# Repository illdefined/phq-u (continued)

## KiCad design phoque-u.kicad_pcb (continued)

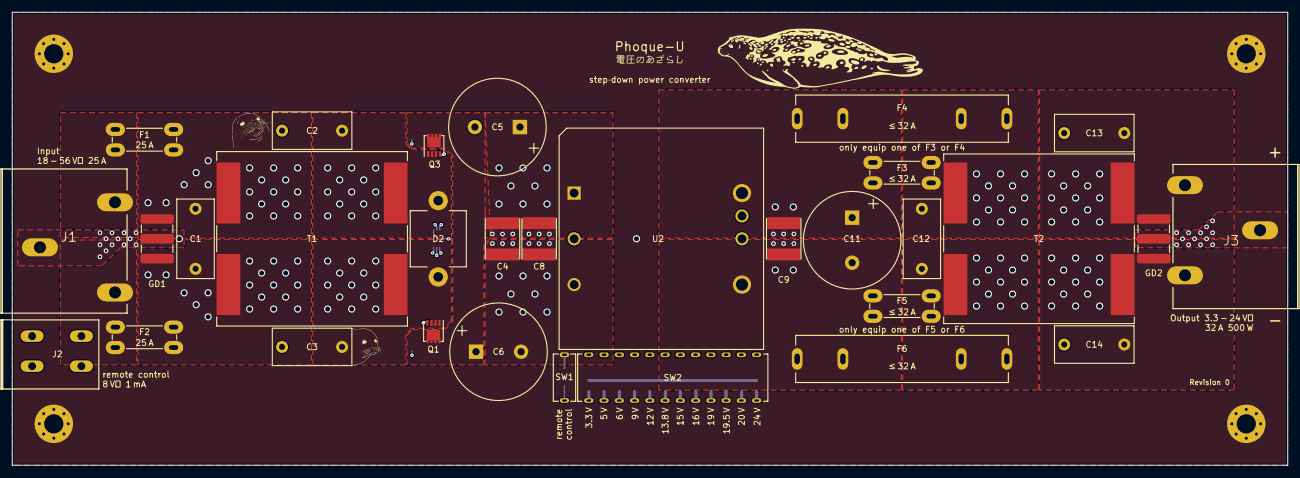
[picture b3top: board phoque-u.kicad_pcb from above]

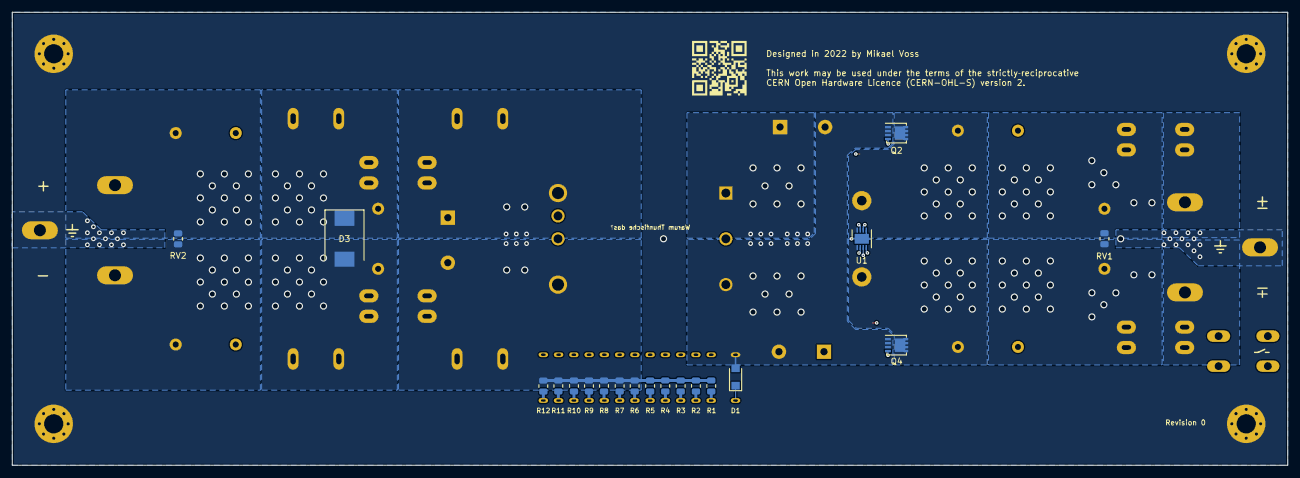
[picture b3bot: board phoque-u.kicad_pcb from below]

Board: 4 copper layers, 212.3 x 75.4 mm, 54 parts (19 on the bottom side), 33 nets.

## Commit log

2022-01-04 Initial import
2022-01-05 Update schematic according to parts availability
2022-01-05 Specify full part number for DC/DC module
2022-01-05 Add footprints
2022-01-05 Replace switches
2022-01-05 i7A4W033A033V: Remove pins 9 & 10
2022-01-05 Sir120DP: Remove pins 6, 7 & 8
2022-01-05 2606-1103: Correct pin numbers
2022-01-05 Remove film capacitors
2022-01-06 Remove test points
2022-01-07 Add initial PCB layout
2022-01-07 Optimise paths between rectifier and converter
2022-01-08 Add dedicated signal and ground layers
    This reduces the board dimensions considerably.
2022-01-08 Cut board to 212.3 × 75 cm
2022-01-08 Add missing 3D models
2022-01-08 Correct zone clearances
2022-01-08 Centre PCB
2022-01-08 Widen board for better fit and add mounting holes
2022-01-08 Customise PCB stackup
2022-01-09 Clean up silkscreen
2022-01-09 Reduce zone clearance to 0.2 mm
    Coating will be much more useful.
2022-01-09 Clear pads from silkscreen
2022-01-09 Attempt to optimise high‐current paths
2022-01-10 Finalise silkscreen
2022-01-10 Remove hyphen‐minus from project name
2022-01-10 Correct zone overlap
2022-01-10 Add JLC order number to silkscreen
2022-01-12 Add remote control circuit details to silkscreen
2022-01-24 Add external symbol and footprint library
2022-01-24 Revise schematic
    - Remove remote on/off connector,
    - remove extra fuses,
    - adjust overvoltage protection values,
    - replace switches with pin headers,
    - replace input and output power connectors,
    - add microcontroller for supervision,
2022-01-24 Add phq_Symbol footprint library
2022-01-24 Complete footprint assignments
2022-02-01 Complete placement and routeing
2022-02-01 phoqueu → phq-u
2022-02-01 Add enclosure connection strip
2022-02-01 Add thermal vias and clean up silkscreen
2022-02-01 Copy earth strips to back
2022-02-01 Add annotations to silkscreen
2022-02-02 Invert project URL QR code
2022-02-02 Exclude ancillary I/O header from BOM
2022-02-02 Exclude optional ground bias resistor from BOM
2022-02-02 Position mounting holes closer to corners
    A distance of 7.5 mm to the edges should provide sufficient mechanical
    stability.
2022-02-02 Add 3.3 V TVS diodes and revise ground zones
2022-02-02 Correct clearance violations
2022-02-02 Re‐route ground traces
2022-02-02 Clean up schematic
2022-02-02 Correct ESP32-C3 pad connection
2022-02-02 Re‐arrange silkscreen items
2022-02-02 Properly centre 3V3 traces
2022-02-02 Connect TC2030 ground pad through via
2022-02-02 Add and adjust vias
2022-02-04 Replace generic I/O with LED connector
2022-02-13 Replace resistors with available variants
2022-02-13 Add revision number to silkscreen
2022-02-26 Add separate ADCs for remote measurements
2022-02-26 Replace common‐mode choke
2022-02-26 Add 100 nF bypass capacitor to ESP32 power input
2022-02-26 Increase power input filter capacitance
